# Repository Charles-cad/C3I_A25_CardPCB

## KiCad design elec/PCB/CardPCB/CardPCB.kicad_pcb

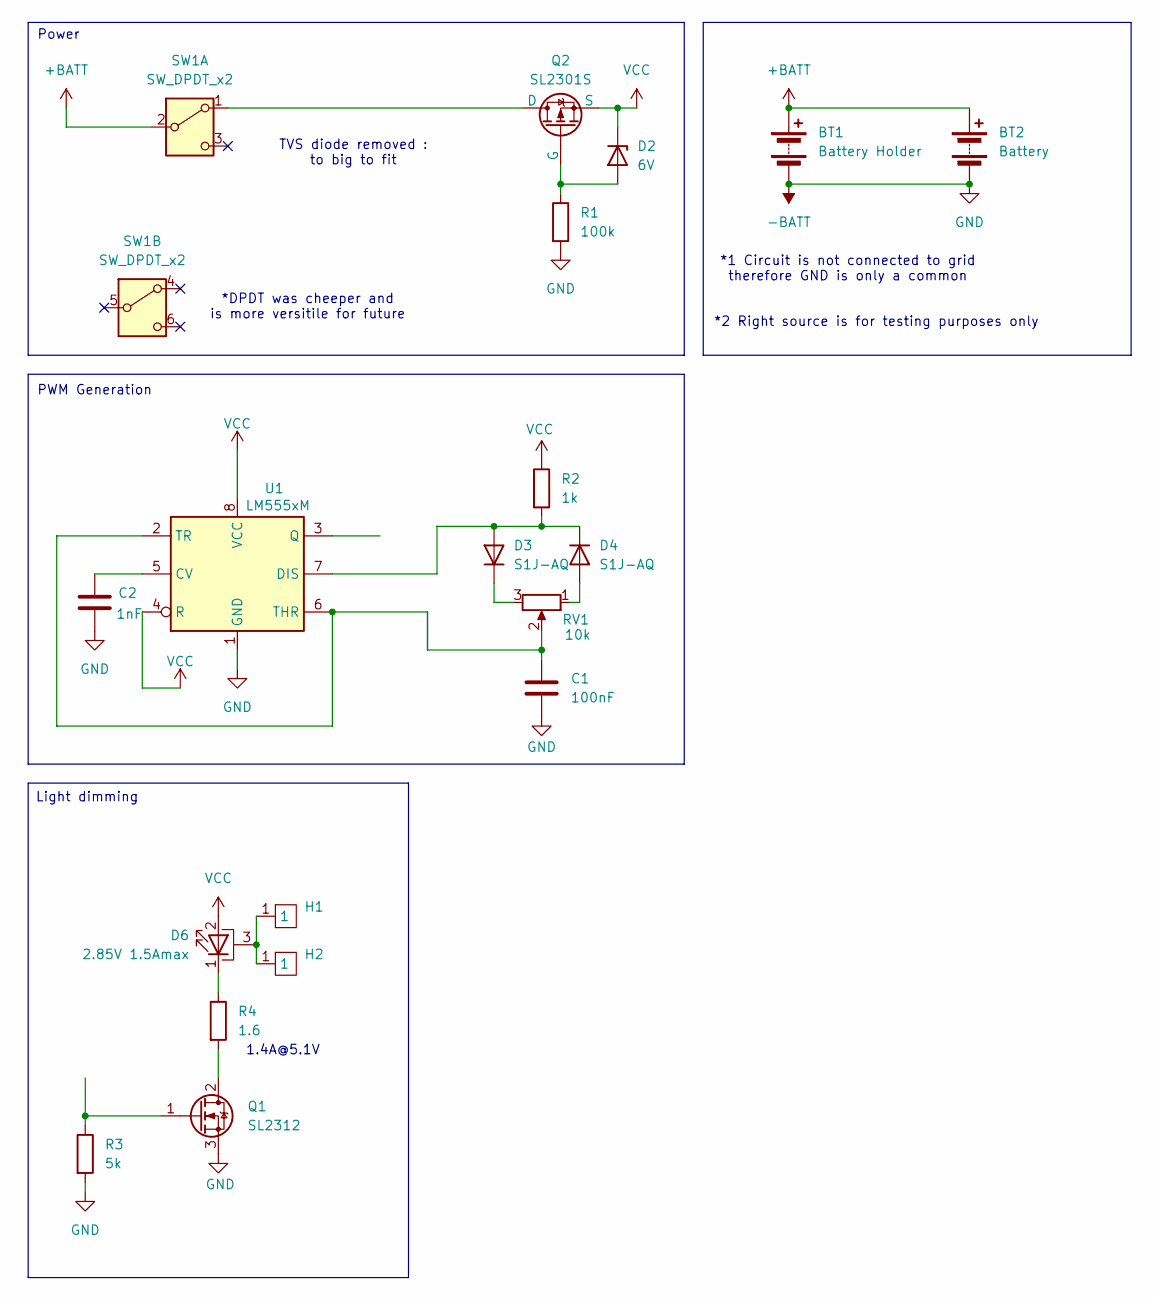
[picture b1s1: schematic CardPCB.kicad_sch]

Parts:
BT1: Battery Holder; BAT_2479
BT2: Battery; 2 pin screw connector
C1: 100nF; C_0805_2012Metric
C2: 1nF; C_0805_2012Metric
D2: 6V; D_SOD-123
D3, D4: S1J-AQ; D_SMB_Handsoldering
D6: 2.85V 1.5Amax; LED_Cree-XHP50_3V_HighDensity
H1, H2: Heatsink
Q1: SL2312; TSOT-23_HandSoldering
Q2: SL2301S; TSOT-23
R1: 100k; R_0805_2012Metric_Pad1.20x1.40mm_HandSolder
R2: 1k; R_0805_2012Metric_Pad1.20x1.40mm_HandSolder
R3: 5k; R_1206_3216Metric_Pad1.30x1.75mm_HandSolder
R4: 1.6; R_1206_3216Metric_Pad1.30x1.75mm_HandSolder
RV1: 10k; Potentiometer_Bourns_TC33X_Vertical
SW1: SW_DPDT_x2; DPDT
U1: LM555xM; SOIC-8_3.9x4.9mm_P1.27mm

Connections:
+BATT: BT1.1 (+), BT2.1 (+), SW1.2 (B)
-BATT: BT1.2 (-), BT2.2 (-), C1.2, C2.2, Q1.3 (S), R1.2, R3.2, U1.1 (GND)
unnamed: D2.2 (A), Q2.2 (G), R1.1
unnamed: D3.2 (A), D4.1 (K), R2.2, U1.7 (DIS)
unnamed: D3.1 (K), RV1.3
unnamed: D4.2 (A), RV1.1
unnamed: D6.1 (K), R4.1
unnamed: D6.3 (PAD), H1.1, H2.1
unnamed: Q1.2 (D), R4.2
unnamed: Q1.1 (G), R3.1
unnamed: Q2.1 (D), SW1.1 (A)
unnamed: C2.1, U1.5 (CV)
unnamed: C1.1, RV1.2, U1.2 (TR), U1.6 (THR)
VCC: D2.1 (K), D6.2 (A), Q2.3 (S), R2.1, U1.4 (R), U1.8 (VCC)

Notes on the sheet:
1.4A@5.1V
*1 Circuit is not connected to grid therefore GND is only a common
Light dimming
TVS diode removed : to big to fit
Power
*DPDT was cheeper and is more versitile for future
PWM Generation
*2 Right source is for testing purposes only

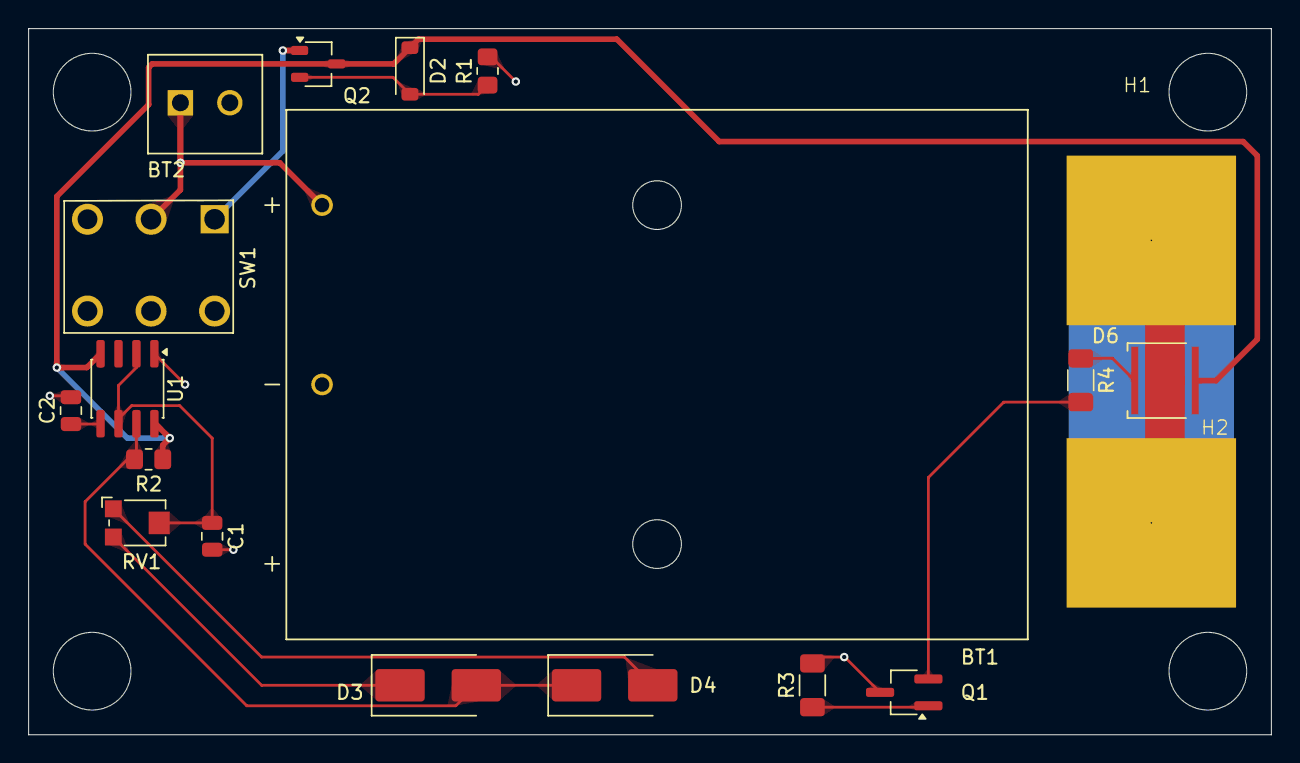
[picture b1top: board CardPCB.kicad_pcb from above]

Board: 2 copper layers, 88.0 x 50.0 mm, 19 parts (0 on the bottom side), 14 nets.

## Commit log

2025-11-20 so many changes
2025-11-29 Final PCB
    Generation of gerber and sending command
2025-11-29 added ground plane and fix qr code
2025-12-28 Added digikey order
2026-01-03 Dossier de remise
    voila
2026-01-03 Gerber dans fichier de remise
